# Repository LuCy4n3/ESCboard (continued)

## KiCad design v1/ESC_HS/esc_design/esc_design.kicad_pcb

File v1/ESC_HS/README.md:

# ESC_HS

**ESC v1.** This project is stored in `v1/ESC_HS/`. The project name remains
`ESC_HS`. See the [repository version index](../../README.md) for both generations
and [ESC_HF v2](../../v2/ESC_HF/README.md) for the newer hardware design.

Run the commands in this guide from the `v1/ESC_HS/` project directory.

Experimental sensorless brushless-motor ESC firmware for an STSPIN32G4-based
power stage. The STM32CubeIDE project targets the STM32G431VB MCU and combines
high-frequency-injection (HFI) startup, six-step acquisition, field-oriented
current control, a back-EMF observer and UART diagnostics.

This is an **experimental build** for bench testing and control/filter research.
The diagnostic current-filter path runs alongside the raw-current control path.
See [EXPERIMENTAL_BUILD.md](EXPERIMENTAL_BUILD.md) for the current experiment,
capture format and validation limits.

**The current firmware initializes its speed target to 2000 RPM and can start the
motor after power-up without a UART command.** Before powering the bridge, review
`FM_TARGET_RPM` in `Core/Inc/fast_motor_config.h`. Set it to `0.0f` and rebuild if
you require a zero target at startup. This cleanup preserves the firmware's
existing behavior and configuration.

## Hardware and BOM status

The supplied KiCad project is in `esc_design/`. See [hardware/BOM.md](hardware/BOM.md)
for the source-derived BOM, component counts and unresolved design fields.
The [Excel BOM](hardware/outputs/esc_hs_bom/BOM.xlsx) includes grouped parts, the
component inventory and review findings. CSV exports are also available in `hardware/`.
The PCB has a duplicated `R34` reference, and several parts still need exact values
or part numbers confirmed before purchasing.

The v2 `ESC_HF` hardware uses STM32H750 + DRV8323 and is a different
design. Its schematic and BOM must not be used as the ESC_HS hardware definition.

## Project contents

| Path | Purpose |
| --- | --- |
| `Core/Src/main.c` | Peripheral setup, UART command parser and foreground service. |
| `Core/Src/fast_motor.c` | Motor state machine, control, protection and capture logic. |
| `Core/Inc/fast_motor_config.h` | Motor model, sensing scales, limits and experiment switches. |
| `Core/Src/stspin_driver.c` | STSPIN gate-driver configuration over I2C. |
| `Core/Src/telemetry.c`, `Core/Inc/telemetry.h` | Telemetry serialization and address definitions. |
| `Core/Src/`, `Core/Inc/` | Experimental current-filter implementation, diagnostics and RAM capture format. |
| `Drivers/` | Bundled STM32 HAL and CMSIS sources, including their license files. |
| `ESC_HS.ioc` | CubeMX peripheral configuration. |
| `.project`, `.cproject`, `.mxproject` | STM32CubeIDE project metadata. |
| `STM32G431VBTX_FLASH.ld` | Linker script: 128 KiB flash and 32 KiB RAM. |
| `tools/` | Capture/export tool matching the current 20 kHz experimental format. |
| `EXPERIMENTAL_BUILD.md` | Current experimental build behavior and validation limits. |
| `esc_design/` | ESC_HS hierarchical KiCad schematic, PCB and local MOSFET footprint library. |
| `hardware/` | BOM exports, source reconciliation and design findings. |
| `tools/export_bom.py` | Rebuild the CSV BOM and report from a KiCad XML netlist. |

## Current source configuration

The authoritative settings are the active source files, rather than the older
README or the locally retained `Debug/` executables.

| Setting | Current source value |
| --- | --- |
| `FM_FIRMWARE_BUILD_ID` | `26101703` |
| MCU system clock | 170 MHz |
| `FM_PWM_HZ` | 40 kHz PWM/control (25 us period) |
| `FM_RUN_RAW_OBSERVER_20KHZ` | `1`: RUN observer experiment at 20 kHz |
| Diagnostic current-filter experiment | Enabled: separate 20 kHz shadow computation |
| Filter-to-observer assist | Disabled |
| UART | USART1, 460800 baud, 8 data bits, no parity, 1 stop bit |
| `FM_TARGET_RPM` / `FM_MAX_RPM` | +2000 / 32000 RPM |
| `FM_POLE_PAIRS` | 7 |
| Current conversion assumptions | 3.3 V ADC reference, 12-bit ADC, gain 5, 5 mOhm shunts |
| Bus-voltage conversion | 21:1 divider |

These values describe the checked-in configuration, not verified ratings for an
unknown board or motor. The motor model is labeled as an A2212/5T 2450 KV starting
model in the source. Review and measure the parameters for the actual hardware.

## Build and flash

1. Install STM32CubeIDE with STM32G4 support and connect an appropriate ST-LINK/SWD
   programmer. The local installation found during cleanup is CubeIDE 1.18.0.
2. In CubeIDE, use **File > Import > General > Existing Projects into Workspace**
   and select this directory. Keep the name `ESC_HS` because project metadata uses it.
3. Select the intended Debug or Release configuration. Review the MCU, linker
   script and motor/sensing settings before building.
4. Use **Project > Clean**, then **Build Project**. Confirm the current sources,
   including the experimental filter module, are compiled and the build fits the
   linker's memory limits.
5. With the power stage in a controlled bench setup, use the IDE's debug/flash
   workflow to program the freshly built ELF. Confirm the reported firmware build
   ID is `26101703` for this source configuration.

Generated outputs normally appear in `Debug/` or `Release/`. Existing binaries are
kept locally and ignored by Git; their presence does not prove they match the source.
The project contains custom peripheral/interrupt code, so review diffs carefully
after regenerating code from the `.ioc` file.

## Connections and initial use

The following are MCU signal assignments from the project. They are not connector
pin numbers; confirm the board wiring using the matching schematic.

| Function | Source assignment |
| --- | --- |
| UART transmit / receive | PA9 / PA10 (USART1 TX / RX) |
| Gate-driver configuration | PC8 / PC9 (I2C3 SCL / SDA), 7-bit address `0x47` |
| Phase PWM pairs | PE9/PE8, PE11/PE10, PE13/PE12 (TIM1 CH1/1N, CH2/2N, CH3/3N) |
| DC bus sensing | PF0, ADC1_IN10 |
| Current-sense paths | OPAMP1/2/3 and ADC2 injected sampling; verify phase order on the board. |

Use a UART adapter compatible with the MCU's 3.3 V logic, cross TX/RX, and connect
the appropriate signal ground. Close other serial programs before opening the
same COM port. The command interface uses binary bytes, not typed ASCII text.

For first operation, use a current-limited supply, secure the unloaded motor and
remove any propeller. Review the nonzero startup target before applying power.
Watch state, fault, bus voltage, phase-current and ISR-overrun telemetry during
commissioning. A firmware trip threshold is not a certified power-stage rating.

## UART commands

Each command is exactly five bytes. Speed is a signed 16-bit RPM target in
big-endian two's-complement form. `main.c` accepts targets from -32000 to +32000.

| Operation | Hex bytes |
| --- | --- |
| Request zero speed / bridge-off idle | `15 07 BB 00 00` |
| Set +1000 RPM | `15 07 BB 03 E8` |
| Set -1000 RPM | `15 07 BB FC 18` |
| Arm a new experimental RAM capture | `15 07 BC 00 00` |

A zero target requests the firmware's idle/coast behavior; it is not an emergency
power disconnect. Closing a serial program does not send a zero target or stop
the motor. Earlier notes referring to command byte `01` do not describe this parser.

Telemetry consists of seven-byte records: `AA 55`, one address byte, and a
little-endian 32-bit payload. Channels serialized with `append_signed_offset`
use an XOR sign bias of `0x80000000`; other channels use their defined unsigned
or integer representation. Consult `telemetry.c` for the active channel set and
`telemetry.h` for addresses and units. Not every defined channel is emitted in
every compile-time mode. Periodic telemetry is nominally every 50 ms.

## Experimental capture and offline analysis

The current RAM format contains 256 consecutive 20 kHz frames (12.8 ms). Each
32-byte frame includes the ISR tick, raw and filtered phase currents, PWM command
registers, bus voltage, filter diagnostics, cycle count and flags. Current values
are quantized at 4 mA/count. Capture collection requires the appropriate RUN mode;
arming a capture does not start or stop the motor.

Create a Python environment and an output directory:

```powershell
python -m venv .venv
.\.venv\Scripts\python.exe -m pip install -r tools/requirements.txt
New-Item -ItemType Directory -Force captures
$captureTool = Get-ChildItem -LiteralPath tools -Filter '*shadow20k.py' -File | Select-Object -ExpandProperty FullName
```

With the motor already commissioned and running in the intended mode, acquire a
capture using the actual serial port:

```powershell
.\.venv\Scripts\python.exe $captureTool --serial COM4 --arm --seconds 20 --out captures/experimental_20k.csv
```

The tool sends only the capture-arm command, receives UART bytes and writes a CSV,
raw `.bin` and `.summary.json`. Serial export sends one RAM frame per telemetry
period, so collecting a full buffer takes about 12.8 seconds after it is ready;
allow more time if RUN has not been reached. Check that the report contains all
256 samples and inspect discontinuities/timing before interpreting results.

Decode a previously recorded raw UART stream without opening a serial port:

```powershell
.\.venv\Scripts\python.exe $captureTool --bin captures/experimental_20k.bin --out captures/experimental_redecoded.csv
```

Do not pass an arbitrary MCU binary or a different capture format to `--bin`.
The neighboring 1024-sample/1 kHz decoders and historical capture profiles target
different formats. Numerical summaries describe signal differences and noise
proxies, not true-current estimation accuracy without an independent reference.

## Git layout and verification

The local repository includes active firmware, HAL/CMSIS sources and licenses,
CubeIDE project files, documentation, the hardware design/BOM and the matching
capture tool. Generated build trees, machine-specific language settings, `.orig`
and `.pre_zc` snapshots, Python environments and `captures/` remain local and ignored.

Source filenames and internal identifiers remain as supplied. Documentation and
offline-tool checks do not replace an ARM build, flashing, timing measurements
or motor tests for this experimental build.

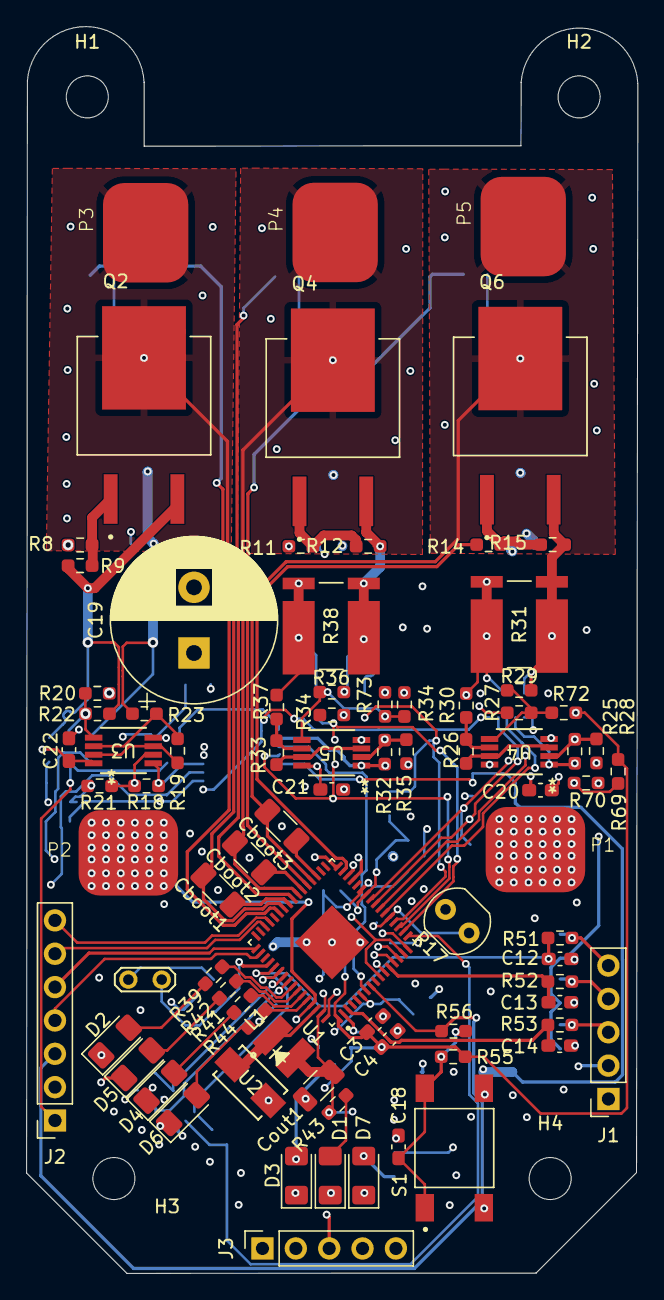
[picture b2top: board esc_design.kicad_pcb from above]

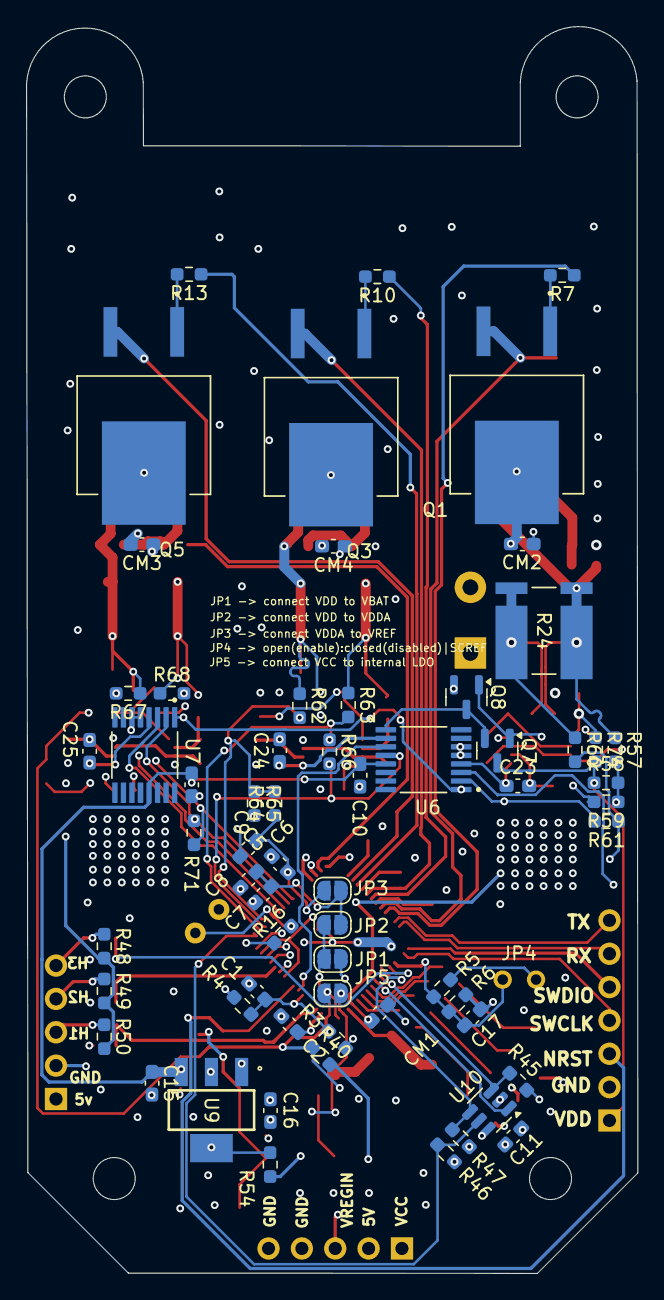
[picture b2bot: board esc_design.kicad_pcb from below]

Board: 4 copper layers, 46.5 x 95.0 mm, 149 parts (63 on the bottom side), 90 nets.

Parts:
C1, C2, C3, C5, C7, C9, C10, C11, C15, C18, C20, C21, C22, C23, C24, C25: 100n; C_0603_1608Metric_Pad1.08x0.95mm_HandSolder
C4, C16: 10u; C_0603_1608Metric_Pad1.08x0.95mm_HandSolder
C6, C8, C17: 1u; C_0603_1608Metric_Pad1.08x0.95mm_HandSolder
C12, C13, C14: 4n7; C_0603_1608Metric_Pad1.08x0.95mm_HandSolder
C19: 220u; CP_Radial_D12.5mm_P5.00mm
CM1, CM2, CM3, CM4: 220n; C_0603_1608Metric_Pad1.08x0.95mm_HandSolder
Cboot1, Cboot2, Cboot3: 1u; C_1206_3216Metric_Pad1.33x1.80mm_HandSolder
Cout1: 10u; C_1206_3216Metric
D1, D2, D3, D4, D5, D6, D7: D; D_1206_3216Metric_Pad1.42x1.75mm_HandSolder
H1, H2, H3, H4: MountingHole; MountingHole_3.2mm_M3
J1, J3: Conn_01x05_Pin; PinSocket_1x05_P2.54mm_Vertical
J2: Conn_01x07_Pin; PinSocket_1x07_P2.54mm_Vertical
JP1, JP2, JP3, JP5: SolderJumper_2_Open; SolderJumper-2_P1.3mm_Open_RoundedPad1.0x1.5mm
JP4: Jumper_2_Bridged; TestPoint_2Pads_Pitch2.54mm_Drill0.8mm
L1: WE-PD2_3521
P1, P2, P3, P4, P5: Conn_Power
Q1, Q2, Q3, Q4, Q5, Q6: IRFS7530PBF
Q7: SQ3427CEV-T1_GE3; SOT-23
Q8: BSS138; SOT-23
R3, R5, R43, R58, R59, R64, R65, R69, R70: 20k; R_0603_1608Metric_Pad0.98x0.95mm_HandSolder
R4, R21, R22, R23, R28, R29, R30, R35, R36, R37, R51, R52, R53, R57, R60, R62, R63, R67, R68: 1k; R_0603_1608Metric_Pad0.98x0.95mm_HandSolder
R6, R45, R46, R47, R48, R49, R50, R61, R66, R71: 10k; R_0603_1608Metric_Pad0.98x0.95mm_HandSolder
R7, R8, R10, R11, R13, R14: 10; R_0603_1608Metric_Pad0.98x0.95mm_HandSolder
R9, R12, R15, R19, R20, R26, R27, R33, R34, R34#2, R55, R72, R73, R74: 100k; R_0603_1608Metric_Pad0.98x0.95mm_HandSolder
R16: R; R_0603_1608Metric_Pad0.98x0.95mm_HandSolder
R17: R; R_LDR_4.9x4.2mm_P2.54mm_Vertical
R18, R25, R32: 50k; R_0603_1608Metric_Pad0.98x0.95mm_HandSolder
R24, R31, R38: WSLP27265L000FEA; RES_WSLP2726L2000FEA
R39, R40, R41, R42, R44, R54: 330; R_0603_1608Metric_Pad0.98x0.95mm_HandSolder
R56: 150; R_0603_1608Metric_Pad0.98x0.95mm_HandSolder
S1: TS04-66-43-BK-100-SMT-TR; SW_TS04-66-43-BK-100-SMT-TR
U1: STSPIN32G4; QFN50P900X900X100-65N
U2: STPS1H100AY; SMA_STM
U3, U4, U5: MAX74810ARMZ-RL; MAX74810ARMZ_ADI
U6, U7: TMUX6136PWR; SOP65P640X120-16N
U9: LD1117S50TR; SOT230P700X180-4N
U10: 93LCxxBxxOT; SOT-23-6

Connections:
+5V: C16.1, C20.1, C21.1, C22.1, J1.1, J3.2, R48.2, R49.2, R50.2, R54.1, U3.8 (V+), U4.8 (V+), U5.8 (V+), U9.2 (OUT), U9.4 (OUT)
/Current Sensing/S_A: C23.1, R18.2, U3.1 (OUT_A), U6.4 (S1B)
/Current Sensing/S_B: C24.1, R32.2, U5.1 (OUT_A), U6.10 (S2A)
/Current Sensing/S_C: C25.1, R25.2, U4.1 (OUT_A), U7.4 (S1B)
/Current Sensing/S_LOW1: Q2.S, R9.1, R22.2, R24.2_1, R24.2_2, R57.1
/Current Sensing/S_LOW2: Q4.S, R12.1, R36.2, R38.2_1, R38.2_2, R62.1
/Current Sensing/S_LOW3: Q6.S, R15.1, R29.2, R31.2_1, R31.2_2, R67.1
/DeMUX/DMUX_AnalogA: U1.13 (PA0), U6.3 (D1)
/DeMUX/DMUX_AnalogB: U1.7 (PF1), U6.11 (D2)
/DeMUX/DMUX_AnalogC: U1.22 (PC5), U7.3 (D1)
/DeMUX/NCompOUT: Q7.2 (S), Q8.3 (D), U6.9 (SEL2)
/Eeprom/MISO: R45.2, U1.55 (PB4), U10.3 (DI)
/Eeprom/MOSI: U1.56 (PB5), U10.1 (DO)
/Eeprom/SCLK: R47.2, U1.54 (PB3), U10.4 (CLK)
/Eeprom/SS: R46.2, U1.17 (PA4), U10.5 (CS)
/HallSensorsFilters/HALL1_IN: J1.3, R50.1, R53.1
/HallSensorsFilters/HALL1_OUT: C14.1, R53.2, U1.3 (PC13)
/HallSensorsFilters/HALL2_IN: J1.4, R49.1, R52.1
/HallSensorsFilters/HALL2_OUT: C13.1, R52.2, U1.12 (PC3)
/HallSensorsFilters/HALL3_IN: J1.5, R48.1, R51.1
/HallSensorsFilters/HALL3_OUT: C12.1, R51.2, U1.53 (PD2)
/Inverter/I_H1: R7.1, U1.43 (GHS1)
/Inverter/I_H2: R10.1, U1.40 (GHS2)
/Inverter/I_H3: R13.1, U1.37 (GHS3)
/Inverter/I_L1: R8.1, U1.29 (GLS1)
/Inverter/I_L2: R11.1, U1.30 (GLS2)
/Inverter/I_L3: R14.1, U1.31 (GLS3)
/Inverter/I_OUT1: Cboot1.2, P3.1, Q1.S, Q2.D, U1.42 (OUT1)
/Inverter/I_OUT2: Cboot2.2, P4.1, Q3.S, Q4.D, U1.39 (OUT2)
/Inverter/I_OUT3: Cboot3.2, P5.1, Q5.S, Q6.D, U1.36 (OUT3)
/Inverter/VM: C19.1, CM1.1, CM2.1, CM3.1, CM4.1, P2.1, Q1.D, Q3.D, Q5.D, R3.1, U1.61 (VM)
/LedArray/LEDARR_1: R44.1, U1.60 (PB9)
/LedArray/LEDARR_2: R41.1, U1.59 (PB8)
/LedArray/LEDARR_3: R42.1, U1.58 (PB7)
/LedArray/LEDARR_4: R39.1, U1.57 (PB6)
/MCU/COMP3+: R61.2, U1.10 (PC1), U1.15 (PA2), U6.2 (S1A)
/MCU/COMP3_OUT: Q7.1 (G), Q8.1 (G), U1.11 (PC2), U6.1 (SEL1), U7.1 (SEL1)
/MCU/OpAmp1+: R57.2, R58.2, R59.1, U1.14 (PA1)
/MCU/OpAmp1-: R60.2, R61.1, U1.16 (PA3)
/MCU/OpAmp2+: R62.2, R64.2, R65.1, U1.20 (PA7)
/MCU/OpAmp2-: R63.2, R66.1, U1.18 (PA5)
/MCU/OpAmp2_OUT: R66.2, U1.19 (PA6), U6.12 (S2B)
/MCU/OpAmp3+: R67.2, R69.2, R70.1, U1.23 (PB0)
/MCU/OpAmp3-: R68.2, R71.1, U1.25 (PB2)
/MCU/OpAmp3_OUT: R71.2, U1.24 (PB1), U7.2 (S1A)
/MCU/SCREF: C17.1, JP4.2 (B), R5.2, R6.1, U1.52 (SCREF)
/MCU/SWCLK: J2.4, U1.50 (PA14)
/MCU/SWDIO: J2.5, U1.49 (PA13)
/MCU/Temp_meas: R16.2, R17.1, U1.21 (PC4)
/MCU/USART1_RX: J2.6, U1.46 (PA10)
/MCU/USART1_TX: J2.7, U1.45 (PA9)
/MCU/nRST: J2.3, R56.2, U1.8 (PG10)
GND: C1.2, C2.2, C3.2, C4.2, C5.2, C6.2, C7.2, C8.2, C9.2, C10.2, C11.2, C12.2, C13.2, C14.2, C15.2, C16.2, C17.2, C18.2, C19.2, C20.2, C21.2, C22.2, CM1.2, CM2.2, CM3.2, CM4.2, Cout1.2, D1.1 (K), D2.1 (K), D3.1 (K), D4.1 (K), D5.1 (K), D6.1 (K), D7.1 (K), J1.2, J2.2, J3.4, J3.5, P1.1, Q8.2 (S), R4.2, R6.2, R17.2, R20.1, R21.2, R23.2, R24.1_1, R24.1_2, R27.1, R28.2, R30.2, R31.1_1, R31.1_2, R34.2, R34#2.1, R35.2, R37.2, R38.1_1, R38.1_2, R59.2, R60.1, R63.1, R65.2, R68.1, R70.2, S1.2, S1.4, U1.32 (PGND), U1.65 (VSS), U2.2, U3.4 (V-), U4.4 (V-), U5.4 (V-), U6.5 (VSS), U6.6 (GND), U7.5 (VSS), U7.6 (GND), U9.1 (GND), U10.2 (GND)
unnamed: C18.1, R55.2, R56.1, S1.1, S1.3
unnamed: C23.2, R18.1, R21.1, U3.2
unnamed: C24.2, R32.1, R35.1, U5.2
unnamed: C25.2, R25.1, R28.1, U4.2
unnamed: D1.2 (A), R43.2
unnamed: D2.2 (A), R39.2
unnamed: D3.2 (A), R40.2
unnamed: D4.2 (A), R41.2
unnamed: D5.2 (A), R42.2
unnamed: D6.2 (A), R44.2
unnamed: D7.2 (A), R54.2
unnamed: Q1.G, R7.2
unnamed: Q2.G, R8.2, R9.2
unnamed: Q3.G, R10.2
unnamed: Q4.G, R11.2, R12.2
unnamed: Q5.G, R13.2
unnamed: Q6.G, R14.2, R15.2
unnamed: R19.1, R23.1, U3.6
unnamed: R19.2, U3.3, U3.7
unnamed: R20.2, R22.1, R74.1, U3.5
unnamed: R26.1, R30.1, U4.6
unnamed: R26.2, U4.3, U4.7
unnamed: R27.2, R29.1, R72.1, U4.5
unnamed: R33.1, R37.1, U5.6
unnamed: R33.2, U5.3, U5.7
unnamed: R34#2.2, R36.1, R73.1, U5.5
unnamed: Cboot1.1, U1.41 (BOOT1)
unnamed: Cboot2.1, U1.38 (BOOT2)
unnamed: Cboot3.1, U1.35 (BOOT3)
unnamed: C1.1, R3.2, R4.1, U1.6 (PF0)
unnamed: L1.1, U1.62 (SW), U2.1
VBAT: C2.1, JP1.2 (B), U1.2 (VBAT)
VCC: C9.1, C10.1, C15.1, Cout1.1, J3.1, JP5.1 (A), L1.2, R43.1, U1.63 (VCC), U6.13 (VDD), U7.13 (VDD), U9.3 (IN)
VDD: C3.1, C4.1, C11.1, J2.1, JP1.1 (A), JP2.1 (A), JP4.1 (A), Q7.3 (D), R5.1, R16.1, R40.1, R45.1, R46.1, R47.1, R55.1, R58.1, R69.1, R72.2, R73.2, R74.2, U1.1 (REG3V3/VDD), U10.6 (VCC)
VDDA: C7.1, C8.1, JP2.2 (B), JP3.1 (A), U1.27 (VDDA)
VREF+: C5.1, C6.1, JP3.2 (B), R64.1, U1.26 (VREF+)
VREGIN: J3.3, JP5.2 (B), U1.64 (REGIN)

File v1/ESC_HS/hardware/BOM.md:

# ESC_HS bill of materials

Generated from the supplied `esc_design/esc_design.kicad_sch` hierarchy
and reconciled against `esc_design/esc_design.kicad_pcb`. Values and
footprint identifiers are preserved as authored. The earlier provisional
hardware checklist is replaced by this source-derived BOM.

## Files

- [Excel BOM](outputs/esc_hs_bom/BOM.xlsx): grouped parts, component inventory and review findings.
- [Grouped CSV](BOM.csv): quantities, references, values, footprints and confirmation notes.
- [Component CSV](BOM_components.csv): each schematic reference, including exclusions and PCB counts.
- [Source data and reconciliation](bom_data.json): extracted fields, findings and source hashes.

## Counts and population rules

- 148 schematic component references across 10 sheets.
- 149 PCB footprints. Duplicate references: R34.
- 140 schematic BOM entries in 36 groups.
- 8 references excluded by the schematic BOM flags. DNP references: 0.
- Schematic-only references: none. PCB-only references: none.

Quantities follow the schematic population flags. The duplicate PCB `R34`
is reported separately and does not silently add another schematic part.
`P1`–`P5` are PCB copper connection pads included by the source BOM flags,
not five separately purchased components. Four mounting holes (`H1`–`H4`)
and four solder jumpers (`JP1`–`JP3`, `JP5`) are excluded. `JP4` remains included.

## Items requiring confirmation

| References | Finding |
| --- | --- |
| D1, D2, D3, D4, D5, D6, D7, L1, R16, R17, U10 | Exact value/part requires selection |
| P1, P2, P3, P4, P5 | PCB copper connection pad; no separate component to purchase |
| Q1, Q2, Q3, Q4, Q5, Q6 | Missing component value; Symbol IRFB7530PbF vs footprint IRFS7530PBF: confirm package/part |
| Q7 | Value SQ3427CEV vs symbol/datasheet Si2319CDS: confirm selected device |
| R34 | Duplicate PCB reference (2 footprints); schematic quantity retained |
| U2 | Schematic/PCB footprint mismatch |

`U2` schematic footprint: `SMA_STM`. PCB footprint:
`STPS1H100AY:SMA_STM`. This identifier comparison does not establish a geometry difference.

Duplicated `R34` locations in the supplied PCB coordinates: F.Cu at (111.79555, 72.575001) mm; F.Cu at (117.325, 71.775) mm.

The BOM preserves specific part-like values such as `STSPIN32G4`,
`WSLP27265L000FEA`, `MAX74810ARMZ-RL` and `TMUX6136PWR`. An explicit MPN
field is left blank where the design has not populated it. No supplier
stock, pricing, approved replacements or missing component ratings are invented.
Passive voltage/power ratings and tolerances, and the unresolved generic
parts above, must be selected before this becomes a purchasing BOM.

## Design portability and review scope

`U1` is explicitly STSPIN32G4, matching the firmware family. This is the
ESC_HS design, separate from the neighboring STM32H750/DRV8323 ESC_HF board.
The included `sym-lib-table` refers to an absolute external path. Only the
IRFS7530PbF custom footprint library is bundled; the other custom footprint
definitions are embedded in the PCB. Bundle external libraries and make
their paths project-relative for portable editing.

The review covers component fields, hierarchy, population flags and
schematic/PCB reconciliation. It does not include full electrical ERC,
layout DRC, device-rating approval or hardware validation. Firmware and
schematic/PCB files have not been altered.

## Regenerate CSV and report

From the `v1/ESC_HS/` project directory in PowerShell:

```powershell
New-Item -ItemType Directory -Force captures
& 'C:\Program Files\KiCad\8.0\bin\kicad-cli.exe' sch export netlist --format kicadxml --output captures/bom_netlist.xml esc_design/esc_design.kicad_sch
python tools/export_bom.py --netlist captures/bom_netlist.xml --pcb esc_design/esc_design.kicad_pcb --out hardware/bom_data.json --csv
```

Adjust the KiCad executable path for your installation. These commands refresh
the CSV files, JSON and this report. The Excel file is a snapshot of this
export and must be refreshed separately after design changes.

## Grouped source BOM

| Qty | Value | References | Footprint |
| ---: | --- | --- | --- |
| 16 | 100n | C1, C2, C3, C5, C7, C9, C10, C11, C15, C18, C20, C21, C22, C23, C24, C25 | Capacitor_SMD:C_0603_1608Metric_Pad1.08x0.95mm_HandSolder |
| 2 | 10u | C4, C16 | Capacitor_SMD:C_0603_1608Metric_Pad1.08x0.95mm_HandSolder |
| 3 | 1u | C6, C8, C17 | Capacitor_SMD:C_0603_1608Metric_Pad1.08x0.95mm_HandSolder |
| 3 | 4n7 | C12, C13, C14 | Capacitor_SMD:C_0603_1608Metric_Pad1.08x0.95mm_HandSolder |
| 1 | 220u | C19 | Capacitor_THT:CP_Radial_D12.5mm_P5.00mm |
| 3 | 1u | Cboot1, Cboot2, Cboot3 | Capacitor_SMD:C_1206_3216Metric_Pad1.33x1.80mm_HandSolder |
| 4 | 220n | CM1, CM2, CM3, CM4 | Capacitor_SMD:C_0603_1608Metric_Pad1.08x0.95mm_HandSolder |
| 1 | 10u | Cout1 | Capacitor_SMD:C_1206_3216Metric |
| 7 | D | D1, D2, D3, D4, D5, D6, D7 | Diode_SMD:D_1206_3216Metric_Pad1.42x1.75mm_HandSolder |
| 2 | Conn_01x05_Pin | J1, J3 | Connector_PinSocket_2.54mm:PinSocket_1x05_P2.54mm_Vertical |
| 1 | Conn_01x07_Pin | J2 | Connector_PinSocket_2.54mm:PinSocket_1x07_P2.54mm_Vertical |
| 1 | Jumper_2_Bridged | JP4 | TestPoint:TestPoint_2Pads_Pitch2.54mm_Drill0.8mm |
| 1 | WE-PD2_3521 | L1 | WE-PD2_3521:WE-PD2_3521 |
| 5 | ~ | P1, P2, P3, P4, P5 | Connector_PCBEdge:Conn_Power |
| 6 | ~ | Q1, Q2, Q3, Q4, Q5, Q6 | IRFS7530PbF:IRFS7530PBF |
| 1 | SQ3427CEV-T1_GE3 | Q7 | Package_TO_SOT_SMD:SOT-23 |
| 1 | BSS138 | Q8 | Package_TO_SOT_SMD:SOT-23 |
| 9 | 20k | R3, R5, R43, R58, R59, R64, R65, R69, R70 | Resistor_SMD:R_0603_1608Metric_Pad0.98x0.95mm_HandSolder |
| 19 | 1k | R4, R21, R22, R23, R28, R29, R30, R35, R36, R37, R51, R52, R53, R57, R60, R62, R63, R67, R68 | Resistor_SMD:R_0603_1608Metric_Pad0.98x0.95mm_HandSolder |
| 10 | 10k | R6, R45, R46, R47, R48, R49, R50, R61, R66, R71 | Resistor_SMD:R_0603_1608Metric_Pad0.98x0.95mm_HandSolder |
| 6 | 10 | R7, R8, R10, R11, R13, R14 | Resistor_SMD:R_0603_1608Metric_Pad0.98x0.95mm_HandSolder |
| 12 | 100k | R9, R12, R15, R19, R20, R26, R27, R33, R55, R72, R73, R74 | Resistor_SMD:R_0603_1608Metric_Pad0.98x0.95mm_HandSolder |
| 1 | R | R16 | Resistor_SMD:R_0603_1608Metric_Pad0.98x0.95mm_HandSolder |
| 1 | R | R17 | OptoDevice:R_LDR_4.9x4.2mm_P2.54mm_Vertical |
| 3 | 50k | R18, R25, R32 | Resistor_SMD:R_0603_1608Metric_Pad0.98x0.95mm_HandSolder |
| 3 | WSLP27265L000FEA | R24, R31, R38 | WSLP27265L000FEA:RES_WSLP2726L2000FEA |
| 1 | 100k | R34 | Resistor_SMD:R_0603_1608Metric_Pad0.98x0.95mm_HandSolder |
| 6 | 330 | R39, R40, R41, R42, R44, R54 | Resistor_SMD:R_0603_1608Metric_Pad0.98x0.95mm_HandSolder |
| 1 | 150 | R56 | Resistor_SMD:R_0603_1608Metric_Pad0.98x0.95mm_HandSolder |
| 1 | TS04-66-43-BK-100-SMT-TR | S1 | TS04-66-43-BK-100-SMT-TR:SW_TS04-66-43-BK-100-SMT-TR |
| 1 | STSPIN32G4 | U1 | STSPIN32G4:QFN50P900X900X100-65N |
| 1 | STPS1H100AY | U2 | SMA_STM |
| 3 | MAX74810ARMZ-RL | U3, U4, U5 | MAX74810ARMZ:MAX74810ARMZ_ADI |
| 2 | TMUX6136PWR | U6, U7 | TMUX6136:SOP65P640X120-16N |
| 1 | LD1117S50TR | U9 | LD1117S50TR:SOT230P700X180-4N |
| 1 | 93LCxxBxxOT | U10 | Package_TO_SOT_SMD:SOT-23-6 |

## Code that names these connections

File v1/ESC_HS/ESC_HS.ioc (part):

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Mcu.Name=STM32G431V(6-8-B)Tx
Mcu.Package=LQFP100
Mcu.UserName=STM32G431VBTx
PA0.Mode=IN1-Single-Ended
PA0.Signal=ADC2_IN1
PA1.Mode=Standalone
PA1.Signal=OPAMP1_VINP
PA10.Mode=Asynchronous
PA10.Signal=USART1_RX
PA2.Mode=Standalone
PA2.Signal=OPAMP1_VOUT
PA3.Mode=Standalone
PA3.Signal=OPAMP1_VINM
PA5.Mode=Standalone
PA5.Signal=OPAMP2_VINM
PA6.Mode=Standalone
PA6.Signal=OPAMP2_VOUT
PA7.Mode=Standalone
PA7.Signal=OPAMP2_VINP
PA9.Mode=Asynchronous
PA9.Signal=USART1_TX
PB0.Mode=Standalone
PB0.Signal=OPAMP3_VINP
PB1.Mode=Standalone
PB1.Signal=OPAMP3_VOUT
PB2.Mode=Standalone
PB2.Signal=OPAMP3_VINM
PB6.Signal=GPIO_Output
PB7.Signal=GPIO_Output
PB8-BOOT0.Signal=GPIO_Output
PB9.Signal=GPIO_Output
PC2.Signal=GPIO_Output
PC5.Mode=IN11-Single-Ended
PC5.Signal=ADC2_IN11
PC8.Mode=I2C
PC8.Signal=I2C3_SCL
PC9.Mode=I2C
PC9.Signal=I2C3_SDA
PE10.Mode=PWM Generation2 CH2 CH2N
PE10.Signal=TIM1_CH2N
PE11.Signal=S_TIM1_CH2
PE12.Mode=PWM Generation3 CH3 CH3N
PE12.Signal=TIM1_CH3N
PE13.Signal=S_TIM1_CH3
PE8.Mode=PWM Generation1 CH1 CH1N
PE8.Signal=TIM1_CH1N
PE9.Signal=S_TIM1_CH1
PF0-OSC_IN.Mode=IN10-Single-Ended
PF0-OSC_IN.Signal=ADC1_IN10
PF1-OSC_OUT.Mode=IN10-Single-Ended
PF1-OSC_OUT.Signal=ADC2_IN10
RCC.HSE_VALUE=8000000
RCC.SYSCLKFreq_VALUE=170000000
RCC.SYSCLKSource=RCC_SYSCLKSOURCE_PLLCLK
board=custom
